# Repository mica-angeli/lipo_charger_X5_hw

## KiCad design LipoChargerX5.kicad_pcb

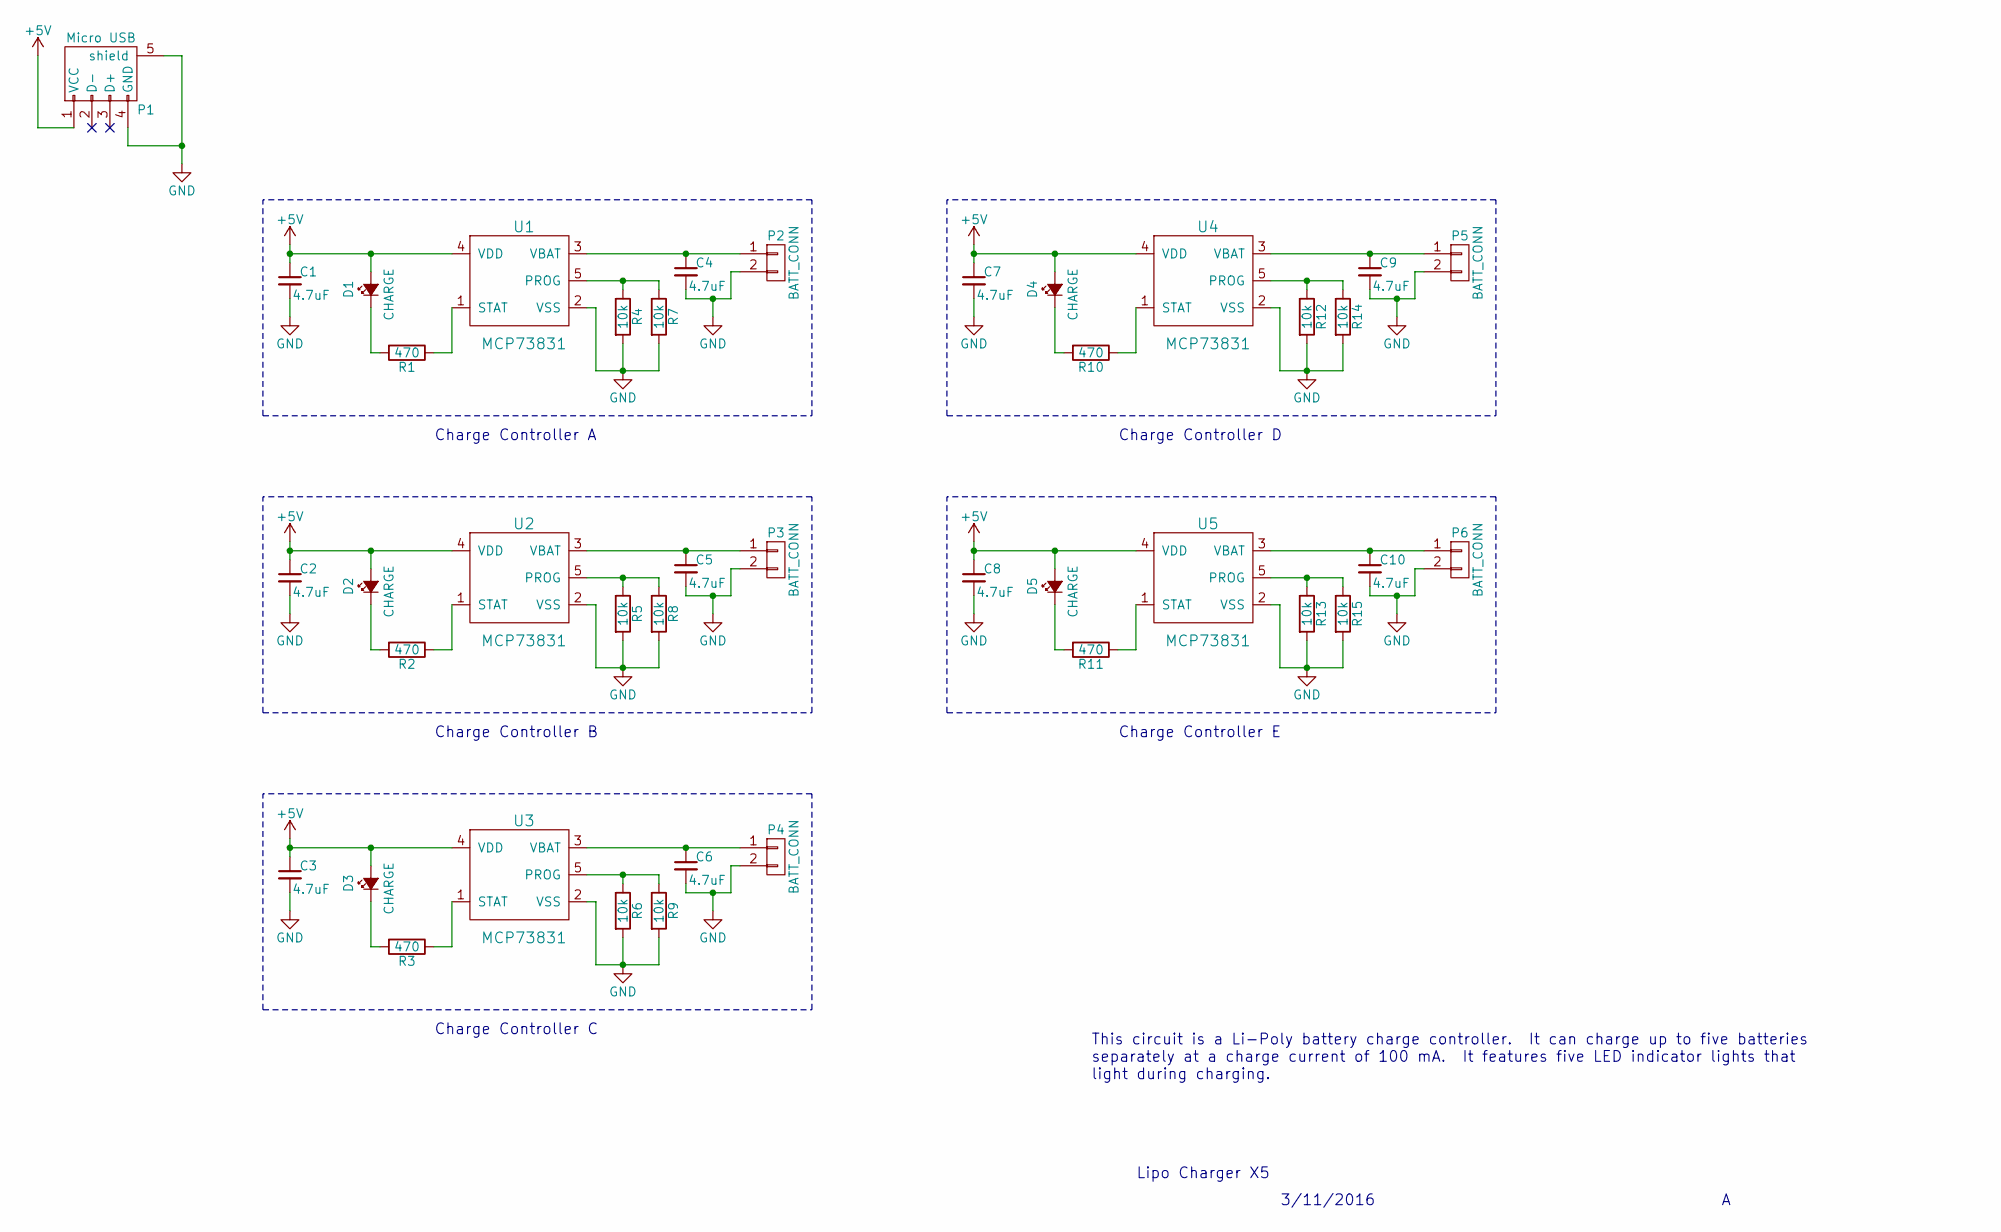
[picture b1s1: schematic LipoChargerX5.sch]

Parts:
C1, C2, C3, C4, C5, C6, C7, C8, C9, C10: 4.7uF
D1, D2, D3, D4, D5: CHARGE
P1: Micro USB
P2, P3, P4, P5, P6: BATT_CONN
R1, R2, R3, R10, R11: 470
R4, R5, R6, R7, R8, R9, R12, R13, R14, R15: 10k
U1, U2, U3, U4, U5: MCP73831; SOT-23-5

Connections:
+5V: C1.1, C2.1, C3.1, C7.1, C8.1, D1.2 (A), D2.2 (A), D3.2 (A), D4.2 (A), D5.2 (A), P1.1 (VCC), U1.4 (VDD), U2.4 (VDD), U3.4 (VDD), U4.4 (VDD), U5.4 (VDD)
GND: C1.2, C2.2, C3.2, C4.2, C5.2, C6.2, C7.2, C8.2, C9.2, C10.2, P1.4 (GND), P1.5 (shield), P2.2, P3.2, P4.2, P5.2, P6.2, R4.2, R5.2, R6.2, R7.2, R8.2, R9.2, R12.2, R13.2, R14.2, R15.2, U1.2 (VSS), U2.2 (VSS), U3.2 (VSS), U4.2 (VSS), U5.2 (VSS)
unnamed: C4.1, P2.1, U1.3 (VBAT)
unnamed: C5.1, P3.1, U2.3 (VBAT)
unnamed: C6.1, P4.1, U3.3 (VBAT)
unnamed: C9.1, P5.1, U4.3 (VBAT)
unnamed: C10.1, P6.1, U5.3 (VBAT)
unnamed: D1.1 (K), R1.2
unnamed: D2.1 (K), R2.2
unnamed: D3.1 (K), R3.2
unnamed: D4.1 (K), R10.2
unnamed: D5.1 (K), R11.2
unnamed: R1.1, U1.1 (STAT)
unnamed: R2.1, U2.1 (STAT)
unnamed: R3.1, U3.1 (STAT)
unnamed: R4.1, R7.1, U1.5 (PROG)
unnamed: R5.1, R8.1, U2.5 (PROG)
unnamed: R6.1, R9.1, U3.5 (PROG)
unnamed: R10.1, U4.1 (STAT)
unnamed: R11.1, U5.1 (STAT)
unnamed: R12.1, R14.1, U4.5 (PROG)
unnamed: R13.1, R15.1, U5.5 (PROG)

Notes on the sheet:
Charge Controller A
This circuit is a Li-Poly battery charge controller. It can charge up to five batteries separately at a charge current of 100 mA. It features five LED indicator lights that light during charging.
Lipo Charger X5
3/11/2016
Charge Controller D
Charge Controller B
Charge Controller E
Charge Controller C

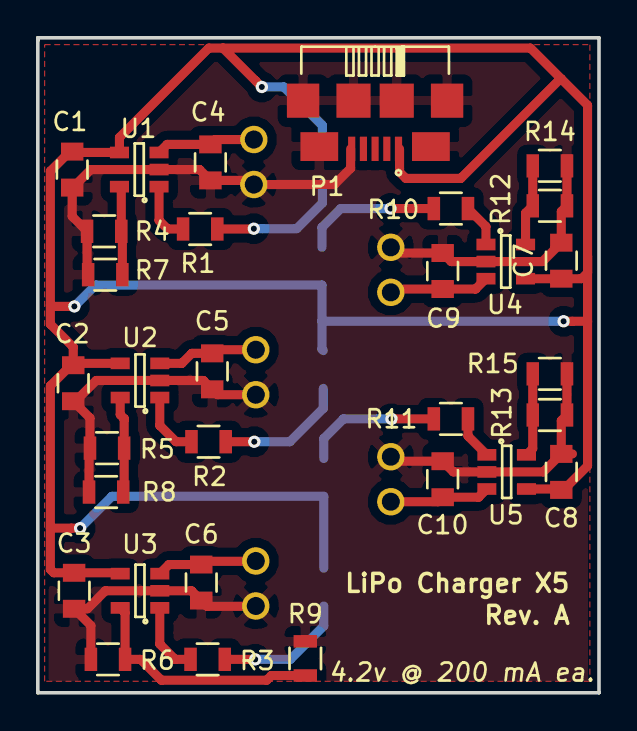
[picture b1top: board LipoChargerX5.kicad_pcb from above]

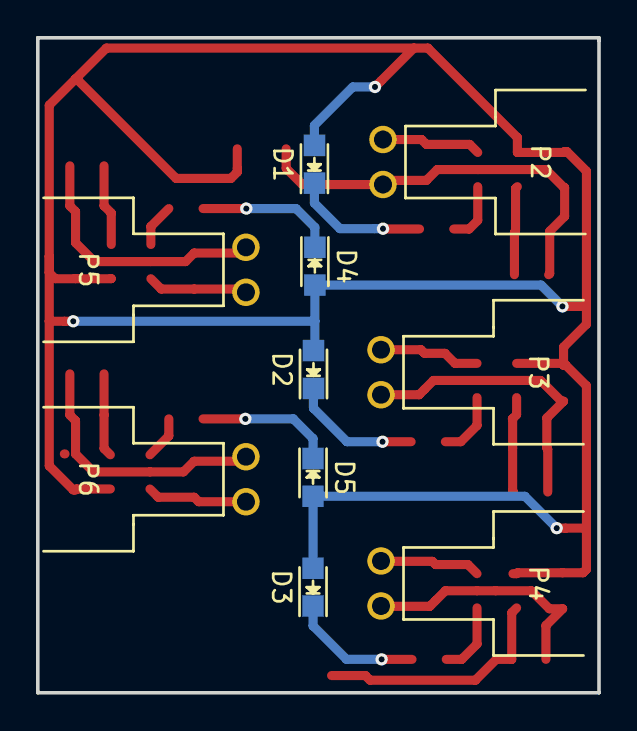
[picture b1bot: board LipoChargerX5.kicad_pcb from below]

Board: 2 copper layers, 31.2 x 36.4 mm, 41 parts (5 on the bottom side), 22 nets.

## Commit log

2016-03-12 Added gitignore
2016-03-12 Finished Rev. A schematic
2016-03-12 Created connector footprint. Associated components. Began PCB layout.
2016-03-12 Finished laying out PCB. Generated gerbers
